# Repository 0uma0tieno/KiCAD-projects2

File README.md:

# KiCAD projects2
 my pcb designs

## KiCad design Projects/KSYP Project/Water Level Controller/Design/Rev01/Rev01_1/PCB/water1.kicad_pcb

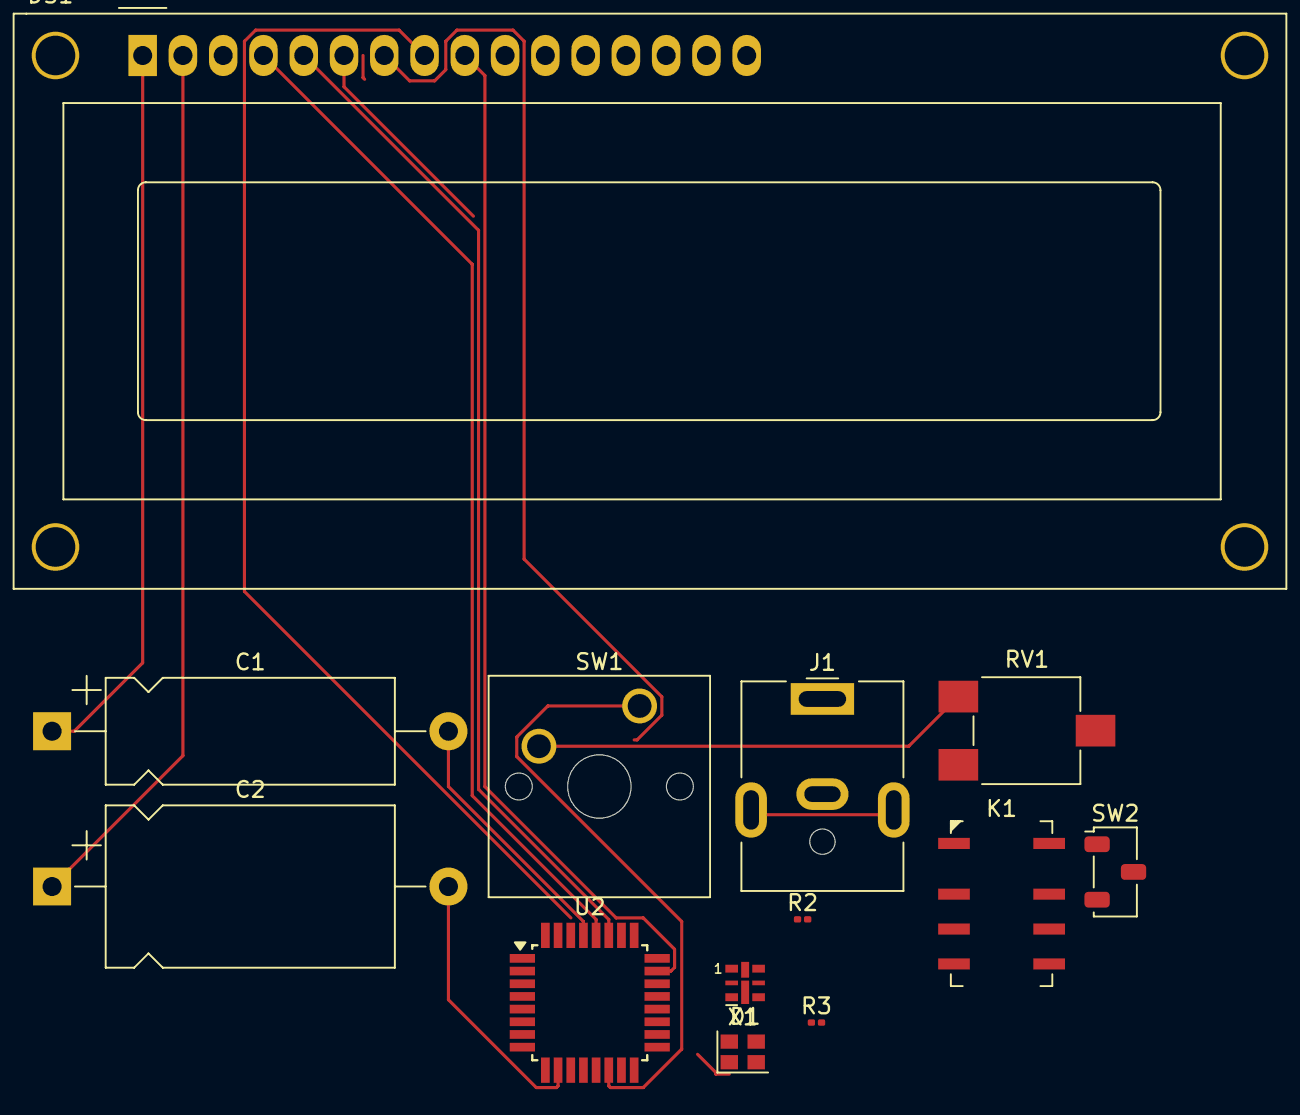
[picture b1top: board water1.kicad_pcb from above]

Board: 2 copper layers, 13 parts (0 on the bottom side), 13 nets.

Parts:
C1: 22pF; CP_Axial_L18.0mm_D6.5mm_P25.00mm_Horizontal
C2: 22pF; CP_Axial_L18.0mm_D10.0mm_P25.00mm_Horizontal
D1: LED; LED-APA102-2020
DS1: WC1602A
J1: Jack-DC; BarrelJack_CUI_PJ-063AH_Horizontal
K1: Relay_DPDT; Relay_2P2T_10x6mm_TE_IMxxG
R2: R; R_0201_0603Metric
R3: 10K; R_0201_0603Metric
RV1: R_Potentiometer; Potentiometer_ACP_CA6-VSMD_Vertical
SW1: SW_SPDT_312; SW_Cherry_MX_1.00u_PCB
SW2: SW_Push; Nidec_Copal_CAS-120A
U2: ATmega328-A; TQFP-32_7x7mm_P0.8mm
X1: SG-211; Oscillator_SMD_SeikoEpson_SG210-4Pin_2.5x2.0mm

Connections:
unnamed: D1.2 (A), R2.1
unnamed: C1.1, D1.1 (K), DS1.1 (VSS), RV1.3, SW1.2 (C), SW2.1, U2.3 (GND), U2.5 (GND), U2.21 (GND)
unnamed: DS1.7 (D0), U2.25 (PC2)
unnamed: DS1.8 (D1), U2.24 (PC1)
unnamed: DS1.9 (D2), U2.23 (PC0)
unnamed: DS1.6 (E), U2.26 (PC3)
unnamed: DS1.4 (RS), U2.28 (PC5)
unnamed: DS1.5 (R/W), U2.27 (PC4)
unnamed: C2.1, DS1.2 (VDD), J1.1, J1.2, RV1.1, U2.4 (VCC), U2.6 (VCC), U2.18 (AVCC)
unnamed: R3.2, SW2.2
unnamed: SW1.1 (B), U2.7 (XTAL1/PB6), U2.14 (PB2)
unnamed: C1.2, R3.1, U2.9 (PD5), U2.29 (~RESET/PC6), X1.4 (Vcc)
unnamed: C2.2, U2.10 (PD6), X1.2 (GND)

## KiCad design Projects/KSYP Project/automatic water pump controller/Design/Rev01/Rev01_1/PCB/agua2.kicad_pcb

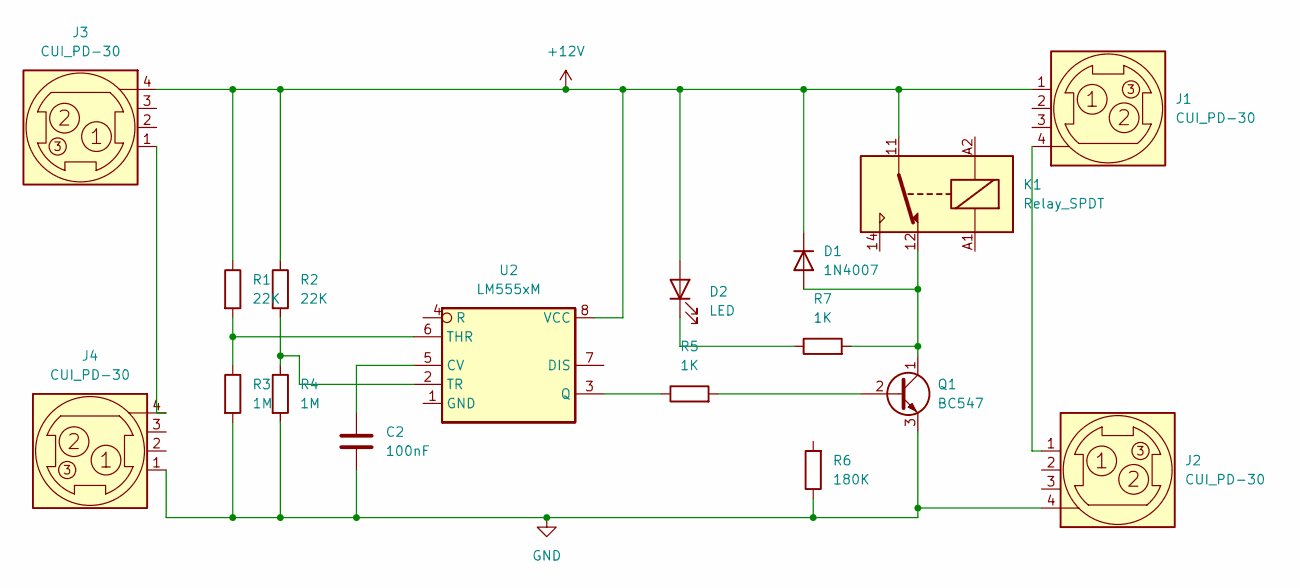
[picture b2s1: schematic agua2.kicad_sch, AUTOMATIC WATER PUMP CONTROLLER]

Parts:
C2: 100nF; CP_Axial_L29.0mm_D13.0mm_P35.00mm_Horizontal
D1: 1N4007; D_DO-41_SOD81_P10.16mm_Horizontal
D2: LED; LED_D3.0mm
J1, J2, J3, J4: CUI_PD-30
K1: Relay_SPDT; Relay_DPDT_Finder_30.22
Q1: BC547; TO-92_Inline
R1, R2: 22K; R_Axial_DIN0204_L3.6mm_D1.6mm_P5.08mm_Horizontal
R3, R4: 1M; R_Axial_DIN0204_L3.6mm_D1.6mm_P5.08mm_Horizontal
R5, R7: 1K; R_Axial_DIN0204_L3.6mm_D1.6mm_P5.08mm_Horizontal
R6: 180K; R_Axial_DIN0204_L3.6mm_D1.6mm_P5.08mm_Horizontal
U2: LM555xM; SOIC-8_3.9x4.9mm_P1.27mm

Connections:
+12V: D1.1 (K), D2.2 (A), J1.1, J3.4 (Shield), K1.11, R1.1, R2.1, U2.8 (VCC)
GND: C2.2, J2.4 (Shield), J4.1, Q1.3 (E), R3.2, R4.2, R6.1
unnamed: D1.2 (A), K1.12, Q1.1 (C), R7.2
unnamed: D2.1 (K), R7.1
unnamed: J1.4 (Shield), J2.1
unnamed: J3.1, J4.4 (Shield)
unnamed: Q1.2 (B), R5.2
unnamed: C2.1, U2.5 (CV)
unnamed: R5.1, U2.3 (Q)
unnamed: R1.2, R3.1, U2.6 (THR)
unnamed: R2.2, R4.1, U2.2 (TR)

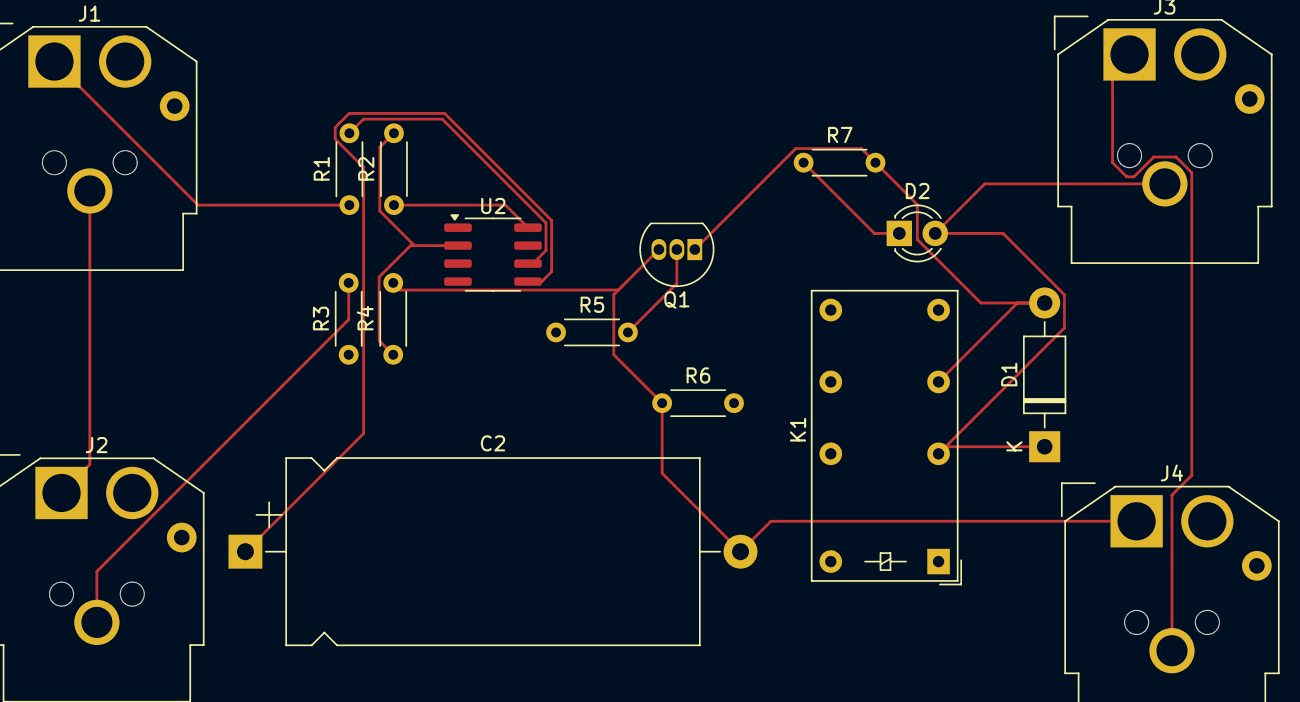
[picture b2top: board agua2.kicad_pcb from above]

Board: 2 copper layers, 17 parts (0 on the bottom side), 11 nets.

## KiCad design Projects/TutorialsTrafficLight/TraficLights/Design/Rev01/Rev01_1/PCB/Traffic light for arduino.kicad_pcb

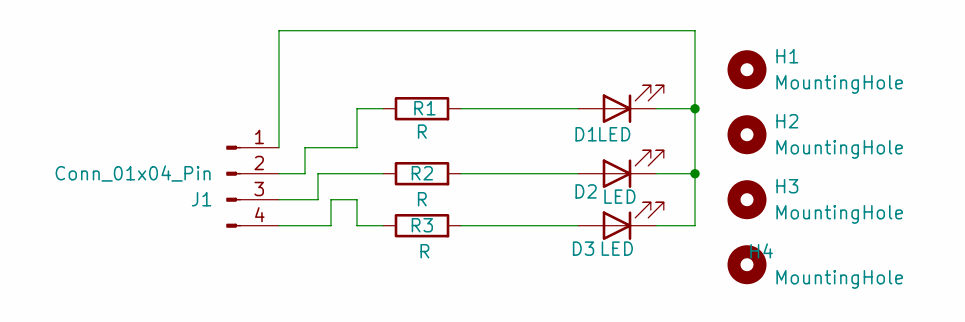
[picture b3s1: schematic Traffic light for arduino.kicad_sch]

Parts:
D1, D2, D3: LED; LED_D3.0mm
H1, H2, H3, H4: MountingHole; MountingHole_2.5mm_Pad
J1: Conn_01x04_Pin; PinHeader_1x04_P2.54mm_Horizontal
R1, R2, R3: R; R_Axial_DIN0204_L3.6mm_D1.6mm_P5.08mm_Horizontal

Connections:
unnamed: D1.2 (A), R1.2
unnamed: D1.1 (K), D2.1 (K), D3.1 (K), J1.1
unnamed: D2.2 (A), R2.2
unnamed: D3.2 (A), R3.2
unnamed: J1.2, R1.1
unnamed: J1.3, R2.1
unnamed: J1.4, R3.1

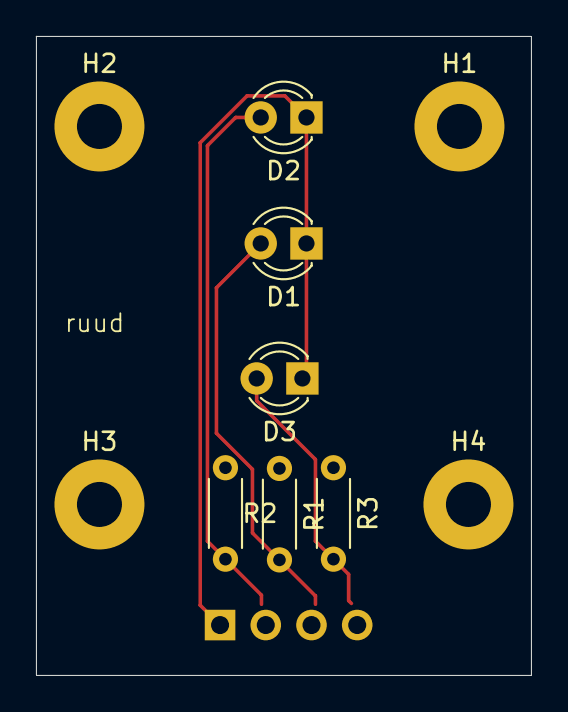
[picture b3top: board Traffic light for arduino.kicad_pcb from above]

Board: 2 copper layers, 27.5 x 35.5 mm, 11 parts (1 on the bottom side), 7 nets.

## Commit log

2024-11-23 update
    just an updated list
